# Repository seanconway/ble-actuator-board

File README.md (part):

# BLE Smart-Lock Board: Hardware Design Spec

**Product:** a pocket-sized container with an IoT smart lock. A Hall switch senses the lid, and a small gearmotor drives a locking bar into place. The board talks to a phone app over Bluetooth LE, charges from USB-C, and has no buttons.
**Scope:** prototype PCB rev 1: schematic, off-board parts, layout, and how the board fits into the enclosure
**Status:** layout complete, ERC/DRC clean (KiCad 10), not yet ordered

| Path | Contents |
|---|---|
| `kicad/ble-actuator-board.kicad_pro` | KiCad 10 project: schematic, PCB, custom design rules (`.kicad_dru`) |
| `kicad/easyeda_lib.pretty`, `kicad/easyeda_lib.3dshapes` | Project-local footprints and 3D models (referenced through the project `fp-lib-table`) |
| `bom.csv` | Bill of materials: MPN, LCSC part number, footprint, package, ratings |

This spec is the reference the schematic and layout are checked against. It turns the product requirements into a buildable design: every part, value, footprint, and pin connection, plus layout rules and bring-up. Requirement IDs (`HW-*`, `EN-*`, `FW-*`, `OI-*`, `CM-*`) are defined in [Appendix A](#appendix-a-requirements-referenced) and [Appendix B](#appendix-b-open-items). Items marked **Proposed** are design choices made here that the requirements do not settle.

Datasheet short names: **PS** = nPM1300 Product Specification v1.3, **MDBT** = Raytac MDBT50Q spec Ver. L, **DRV8213** = TI SLVSGV9, **DRV5032** = TI DRV5032. Reference designators are the ones in `kicad/ble-actuator-board.kicad_sch`. Test pads carry signal-name references on the PCB (see §4.10).

**Design rule for this board:** no DNP parts and no 0 Ω resistors except where bench work is expected to need them. DNP is used only to keep JLC from placing a part at a footprint: U4 and M1 (off-board parts whose symbols carry their own wire-pad footprints) and the test pads TP1–TP16 (bare pads, nothing to place). No on-board component footprint is left unpopulated. The board has two fitted 0 Ω resistors: R2 (the VBAT current-measurement link) and R10 (the GAINSEL strap, lifted to change the gain range). The rework options this rule removed, and what each would have bought, are listed in §13.

---

## 1. Block diagram

```
                        ┌──────────────────────── PCB ────────────────────────┐
 USB-C (6-pin) ─ESD─────┤ VBUS ─► nPM1300                                     │
  CC1/CC2 ─ESD──────────┤          ├─ VBAT ◄── R2 ◄──────── J2 (JST-PH) ◄─────┼── 1S LiPo (2-wire)
                        │          ├─ NTC ◄── TH1 (on board)                  │
                        │          ├─ VSYS ─┬─ RGB LED anode                  │
                        │          │        │   cathodes ◄─ LED0/1/2 sinks    │
                        │          ├─ BUCK2 3V0 ─► MDBT50Q VDD/VDDH          │
                        │          │              DRV5032 VDD ────────────────┼── U4 pads → off-board lid sensor
                        │          ├─ BUCK1 VMOT ─► DRV8213 VM + VCC ─► motor ┼── M1 pads → gearmotor (lock)
                        │          ├─ TWI ◄────────► nRF (I²C master)         │
                        │          ├─ GPIO1 (PMIC_INT) ─► nRF                 │
                        │          └─ GPIO0 (NRESETOUT) ─► nRF nRESET         │
                        │                                                     │
                        │ MDBT50Q-P1MV2 ─ PWM ±──► piezo (differential)       │
                        │               ─ IN1/IN2 ─► DRV8213 (auto-sleep)    │
                        │               ◄ nFAULT/nSTALL, IPROPI (ADC)         │
                        │               ◄ HALL_SENSE (GPIO SENSE)             │
                        │               ─ SWD ─► Tag-Connect (J3)             │
                        └─────────────────────────────────────────────────────┘
```

BUCK2 supplies `3V0` because only VSET2 can select 3.0 V at power-up; BUCK1 supplies `VMOT` (§2, D2).

## 2. Datasheet constraints that shape the design

These findings from the datasheets override or refine the original requirements' assumptions. The schematic reflects all of them.

| # | Constraint | Source | Design consequence |
|---|---|---|---|
| D1 | The DRV8213 RTE package has **no nSLEEP pin**. It sleeps when IN1 = IN2 = 0 for t_AUTOSLEEP (0.75–1.05 ms), drawing ≤20 nA on VM and ≤12 nA on VCC. IN1/IN2 have internal 100 kΩ pull-downs. | DRV8213 §6, §8.5.2 | No external pull-downs on IN1/IN2. HW-3 is met by IN1 = IN2 = 0 plus BUCK1 (`VMOT`) off. |
| D2 | **Only VSET2 can select 3.0 V at power-up.** The VSET1 table tops out at 2.7 V (250–500 kΩ); VSET2 selects 3.0 V with 150 kΩ. The resistor must be ≤5% tolerance. | PS Tables 17, 18 | BUCK2 is the always-on `3V0` rail: R3 = 150 kΩ 1% on VSET2 boots it directly at 3.0 V, so no firmware voltage change is needed after a PMIC power cycle. BUCK1 is `VMOT`. |
| D3 | Grounding a VSET pin holds that buck **off at power-up** under software control. | PS §6.3.1 | VSET1 tied directly to GND, so BUCK1 (`VMOT`) stays off until firmware enables it. Matches FW-A1. |
| D4 | DRV8213 **VREF ≤ min(3.3 V, VM − 1.25 V) = 1.75 V** at VM = 3.0 V. With SMODE = Hi-Z the driver ignores VREF and uses 510 mV internally. | DRV8213 §7.3, §8.4.2.2 | VREF comes from a divider on VMOT, never a rail. SMODE is strapped Low so the divider is used. |
| D5 | **ITRIP target is ~40–65 mA, not ~200 mA.** INEED rates the 699:1 at 220 g·cm and the 136:1 at 140 g·cm, both at 60 mA, so ≤150 g·cm sits at or below ~60 mA. 60 mA is the boundary between DRV8213 gain ranges. | INEED motor spec, DRV8213 Table 8-3 | GAINSEL strapped High by fitted 0 Ω R10: 4900 µA/A, accurate over 10–60 mA, OCP ≥160 mA (below the buck's 200 mA rating). This range brackets the ≤150 g·cm point for both gearboxes. The Hi-Z range (60–350 mA) would start the 699:1 at ~220 g·cm, above HW-2. Lift R10 for Hi-Z only if calibration needs more than 60 mA. |
| D6 | nPM1300 watchdog → **NRESETOUT on a GPIO** resets the host without power-cycling BUCK2 (`3V0`). | PS §7.3.2 | GPIO0 wired to nRF nRESET. The RTC survives a watchdog reset. |
| D7 | The VBUS current limit starts at **100 mA** until firmware writes VBUSINILIM0 and TASK.UPDATE.ILIMSW, and reverts on every replug and reset. | PS §6.1.3 | Covered by FW-B6. Firmware reapplies it on each VBUS-insert event. |
| D8 | Module pins 3–14, 50, 52, 54, and 56–61 are **standard drive, low-frequency (≤10 kHz) only**. PWM and I²C do not count as low frequency. | MDBT §2.5–2.6 | The pin map (§5) keeps PWM, I²C, and motor lines off these pins. IPROPI (analog) is allowed there. |
| D9 | VBUSOUT needs a decoupling capacitor even when unused. Unused LDO/load-switch pins go to GND. | PS §6.1.5, Fig 63 | C8 on VBUSOUT; LSIN/LSOUT pins grounded. |
| D10 | The nPM1300 LED pins are 5 mA current sinks. | PS §6.5 | No LED series resistors. |
| D11 | nPM1300 GPIO0/GPIO1 boot as inputs with a 500 kΩ pull-down. On nRESET this draws ~6 µA against the nRF's reset pull-up until firmware makes it an output. | PS §6.6.1 | Firmware configures GPIO0 early in boot (§12). |
| D12 | The DRV8213 tri-level inputs (GAINSEL, IMODE, SMODE) are biased by internal 75 kΩ to VCC and 130 kΩ to GND, and the datasheet does not say whether that bias is switched off in sleep. A hard strap against it would draw ~23 µA (IMODE high) plus ~40 µA (SMODE low). The logic pins (IN1, IN2, GAINSEL, IMODE, SMODE, nFAULT, nSTALL) are rated −0.3 to 5.75 V **to GND, not to VCC**; only TINRUSH (≤ VCC) and IPROPI (≤ VM + 0.3 V) track a supply. The RTE package allows VCC = VM. | DRV8213 §7.1, Fig 8-15 | The whole driver runs from `VMOT`: VCC, IMODE, the GAINSEL strap (R10), and the nFAULT/nSTALL pull-up (R6). With BUCK1 off the driver is unpowered, so strap bias, R6, and R10 draw nothing in sleep. Driving IN1/IN2 while VMOT is off stays within the absolute maximum ratings. |

## 3. Power design

### 3.1 Rails (net names)

| Net | Source | Voltage | Loads | Notes |
|---|---|---|---|---|
| `VBUS` | USB-C (J1) | 5 V | nPM1300 VBUS only | Input limit 500 mA set by firmware (FW-B6, D7) |
| `VBAT` | Battery (J2) through R2 | 3.0–4.2 V | nPM1300 VBAT only | Nothing else may load VBAT (PS §8.2). Charge temperature comes from the board NTC TH1 (§4.2). |
| `VSYS` | nPM1300 pin 20 | ≈VBAT (1 A max) | PVDD, LED anode | Green and blue are fully lit only while VSYS exceeds their Vf plus 0.5 V sink headroom (§4.8) |
| `3V0` | BUCK2 (VOUT2) | 3.0 V (set by VSET2 at power-up) | nRF VDD/VDDH, VDDIO, lid sensor (through R12), I²C and reset pull-ups, Tag-Connect VCC | Always on outside ship mode (D2). Full-board plane on L3 (§7.1). |
| `VMOT` | BUCK1 (VOUT1) | 3.0 V (set by firmware) | DRV8213 VM and VCC, IMODE, GAINSEL strap (R10), nFAULT pull-up (R6), VREF divider | **Enabled only during actuation** (FW-A1, D3). Never feed the motor from VSYS (HW-1). |
| `GND` | — | 0 V | — | Solid plane on L2 (In1.Cu), §7.1 |

### 3.2 Requirements checklist

Checked against the schematic and layout; unchecked items need bench data.

- [ ] BUCK1 (`VMOT`) output capacitance sized for motor inrush. Confirm 200 mA headroom against measured stall current (OI-H1).
- [x] Every buck output capacitor (C10, C6) keeps ≥4 µF effective capacitance at its 3.0 V DC bias, with ESR ≤50 mΩ (PS Table 20). All 10 µF parts are Samsung CL10A106MA8NRNC (X5R 25 V 0603), Nordic's Configuration 1 part. C1 and C12 use the same part.
- [x] DRV8213 VM bulk (C12, 10 µF) and 0.1 µF bypass (C11) placed at the pin.
- [ ] ITRIP set by R7 (R_IPROPI) and the VREF divider so stall current stays below 200 mA **and** stall torque is ≤150 g·cm (HW-2). R7 is 0603 so it can be swapped after bench calibration (OI-H2).
- [x] VREF from a divider on VMOT (R9/R8), ≤1.75 V (D4). It draws nothing while BUCK1 is off.
- [x] DRV8213 sleep relies on IN1 = IN2 = 0 and its internal pull-downs (D1). No external parts.
- [x] DRV8213 VCC, IMODE, R10, and R6 on `VMOT`, so the driver is unpowered whenever BUCK1 is off (D12). SMODE tied to GND.
- [x] nPM1300 GPIO0 wired directly to nRF nRESET (D6).
- [x] Receptacle CC1/CC2 wired directly to nPM1300 CC1/CC2. No discrete pull-downs; the internal Rd presents the sink (HW-11). A 5.1 kΩ in parallel would put the combined Rd (~2.55 kΩ) out of spec.
- [x] SHPHLD routed to a test pad only. It has an internal 50 kΩ pull-up (HW-6).
- [x] nPM1300 GPIO1 routed to an nRF GPIO as the PMIC interrupt (HW-12).
- [ ] Board NTC TH1 (10 kΩ) from the nPM1300 NTC pin to GND with no capacitor >100 pF on it (PS §6.2.4) ✓. **Placement does not yet follow §4.2:** TH1 sits mid-board about 3.5 mm from U2's body, not at the board edge by the battery. Firmware sets 10 kΩ and TH1's β in ADCNTCRSEL.

### 3.3 Sleep current budget (target ≤10 µA average, FW-B4)

| Contributor | Estimate | Source |
|---|---|---|
| nRF52840 System ON, RTC + LFRC, RAM retention | ~2–3 µA | nRF52840 PS |
| nPM1300 quiescent (BUCK2 on, hysteretic mode) | ~1–2 µA (check PS) | nPM1300 PS |
| DRV5032FB | ~0.69 µA typ at 3 V (1.8 µA max; the 0.54 µA figure is at 1.8 V) | DRV5032 PS |
| DRV8213 in sleep | ~0 µA (unpowered: VM and VCC both on `VMOT`) | HW-3, D12 |
| Resistor leakage (pull-ups, VREF divider) | ~0 µA (see §11, sleep-leak audit) | Design |
| LFRC calibration (periodic) | TBD | OI-F10 |
| Leakage (ESD, LED) | TBD | Measure |
| **Total** | **TBD (OI-F7)** | PPK2 on first build, across R2 |

Advertising is budgeted separately (OI-F5).

## 4. Schematic, by subsystem

Passive defaults: `Capacitor_SMD:C_0402_1005Metric` / `Resistor_SMD:R_0402_1005Metric`. **0603** (`C_0603_1608Metric` / `R_0603_1608Metric`) is used for the 10 µF, 2.2 µF, and 1 µF capacitors, for R2, R3, R7, and R10, and for TH1. Every footprint is listed in `bom.csv`.

### 4.1 USB-C input and ESD (J1, D1–D3, C3)

| Ref | Value / part | Footprint | Connections |
|---|---|---|---|
| J1 | **Same Sky UJC-H-G-SMT-2-P6-TR** (LCSC C45343229): USB-C 6-pin power-only, horizontal top-mount. 5 A / 30 V, 10,000 mating cycles. Four through-hole shell legs in plated slots carry the plug load, so the board needs a through-hole solder step for them. | KiCad stock `Connector_USB:USB_C_Receptacle_GCT_USB4125-xx-x-0190_6P_TopMnt_Horizontal`. Checked against the Same Sky recommended layout (datasheet p.3): same pad row (pitches 1.00 / 3.04 / 5.50 mm, widths 0.70 / 0.76 / 0.80 mm, 1.20 mm tall), same four 0.60 × 1.20 mm slots in 1.10 × 1.70 mm pads at 8.64 × 3.80 mm, same 0.68 mm pad offset from the front slots. The 3D model is the GCT part. The receptacle mouth overhangs the board edge by ~0.6 mm. | A9/B9 VBUS → `VBUS`. A12/B12 GND and SH → GND. A5 CC1 → U2.23. B5 CC2 → U2.24. |
| D1 | **LRC LTVS16H12T5G** (LCSC C172439): unidirectional TVS. V_RWM 12 V, V_BR 12.5 V min, V_C 16 V max at 10 A and 23 V max at 60 A (8/20 µs), ±30 kV IEC 61000-4-2. Requirement: unidirectional; V_BR well above the 5.5 V VBUS maximum; clamp < 22 V (nPM1300 VBUS absolute maximum) at the ~30 A peak of an IEC 61000-4-2 8 kV contact strike. This part gives ~19 V at 30 A (datasheet Fig. 3). | Custom `imports:DFN1610-2L_L1.6-W1.0-P1.22` (below) | Pad 1 (cathode) → `VBUS`, pad 2 (anode) → GND. |
| D2, D3 | **onsemi ESD9B5.0ST5G** (LCSC C111566): bidirectional ESD, V_RWM 5.0 V, V_BR 5.8 V min, 15 pF, I_R ≤100 nA, IEC 61000-4-2 ±18 kV. Requirement: V_RWM ≥ 5.0 V and V_BR(min) > 5.5 V (the nPM1300 CC absolute maximum), bidirectional OK. | `Diode_SMD:D_SOD-923` (1.0 × 0.6 mm): machine placement only | D2 on CC1, D3 on CC2, each to GND |
| C3 | 1.0 µF X7R 50 V (Samsung CL10B105KB8NQNC). Requirement: X5R or better, ≥10 V. | 0603 | `VBUS` to GND at U2.21 (PS Table 39 "C1") |

**Why D1 is unidirectional:** VBUS only ever carries positive voltage, but ESD testing (IEC 61000-4-2) and hot-plug ringing hit it with both polarities. The nPM1300's VBUS pin is rated −0.3 V minimum (PS Table 4). A unidirectional TVS conducts forward on a negative strike and holds VBUS to a forward drop: 1.2 V max at 10 mA for D1, rising to a few volts at ESD current. A bidirectional TVS lets VBUS swing to its full negative breakdown (about −8 V) before clamping, which pushes the strike current through the PMIC's own pin-protection instead. Unidirectional parts also clamp lower on positive strikes than bidirectional parts of the same size. CC1/CC2 carry low-current signals and may use either type.

**Why a 12 V working voltage:** the nPM1300 disconnects VBUS above 5.5 V (VBUSOVP, PS §6.1.2) and survives up to 22 V. With V_BR ≥ 12.5 V, a faulty 9 V or 12 V charger only trips the PMIC's overvoltage cutoff, and the TVS does not conduct. A 6–7 V TVS would carry the charger's full current on the same fault until it failed. The trade-off is a higher clamp, which still stays under 22 V at ESD current.

**Why a 5 V working voltage is enough on CC:** with the nPM1300's internal Rd present, CC sits at about 2.1 V or less, even when the charger advertises 3 A. The ESD part must not conduct below the nPM1300's 5.5 V CC absolute maximum, which D2/D3 guarantee through V_BR ≥ 5.8 V. Their working voltage (5.0 V) only sets the leakage rating, which is ≤100 nA and flows only while a cable is attached.

**D1 footprint (DFN1610-2, LRC land pattern, datasheet p.4):** two pads 0.62 × 1.00 mm at 1.22 mm pitch (0.60 mm gap, 1.84 mm overall). Pad 1 = cathode. The part is leadless and needs reflow or hot air.

**Layout (as built)**
- D1, D2, and D3 sit 2–4 mm from the J1 pads, before the traces reach anything else.
- VBUS is routed at 0.5 mm (0.25 mm neck-down at pads), short and direct to U2.21.
- J1's shell slots are on the GND pour.

### 4.2 Battery and charge temperature sensing (J2, BT1, R2, C4, TH1)

| Ref | Value / part | Footprint | Connections |
|---|---|---|---|
| J2 | **JST S2B-PH-SM4-TB(LF)(SN)** (LCSC C295747): 2-pin JST-PH header, 2.0 mm pitch, SMD right-angle. Placed by JLC. Symbol `Device:Battery`, so the cell is drawn by J2 itself. | `Connector_JST:JST_PH_S2B-PH-SM4-TB_1x02-1MP_P2.00mm_Horizontal` | Pin 1 (+) → R2 → `VBAT`. Pin 2 → GND. |
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
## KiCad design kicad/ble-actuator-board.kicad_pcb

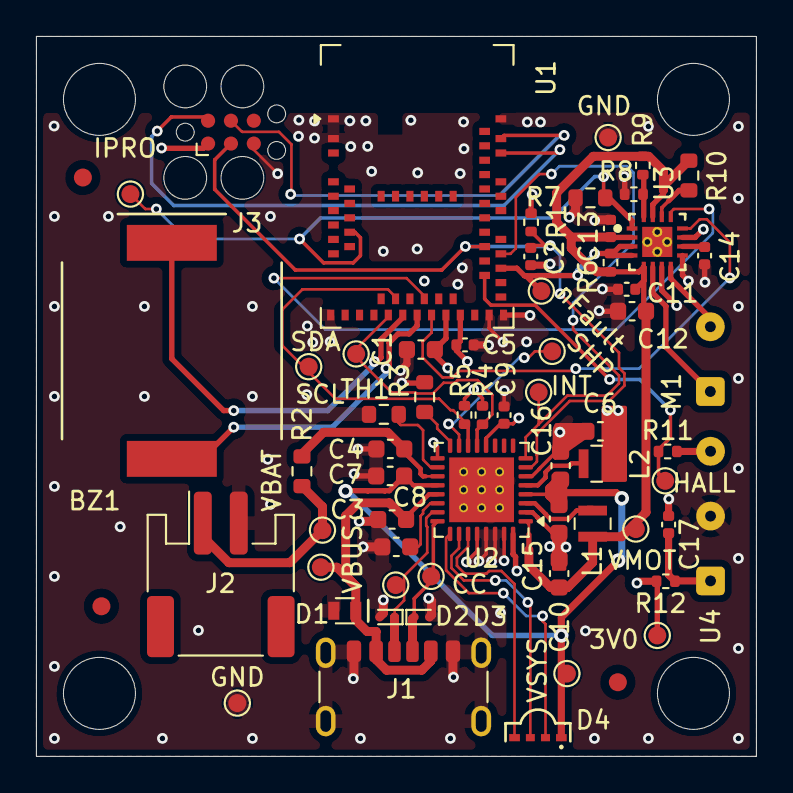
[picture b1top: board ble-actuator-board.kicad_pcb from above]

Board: 4 copper layers, 40.0 x 40.0 mm, 61 parts (0 on the bottom side), 38 nets.

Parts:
3V0: 3V0; TestPoint_Pad_D1.0mm
BZ1: KLJ-1230; BUZ-SMD_L12.0-W12.0
C1, C6, C7, C10, C12, C15, C16: 10uF; C_0603_1608Metric
C2, C5, C9, C11, C13, C17: 100nF; C_0402_1005Metric
C3, C8: 1uF; C_0603_1608Metric
C4: 2.2uF; C_0603_1608Metric
C14: 2.2nF; C_0402_1005Metric
CC: CC2; TestPoint_Pad_D1.0mm
D1: LTVS16H12T5G; DFN1610-2L_L1.6-W1.0-P1.22
D2, D3: ESD9B5.0ST5G; D_SOD-923
D4: NH-B1515RGBA-GF; LED-SMD_4P-L3.2-W1.5_P4-1204RGBWS2-1.5T-A
GND: GND; TestPoint_Pad_D1.0mm
GND#2: GND; TestPoint_Pad_D1.0mm
HALL: HALL_SENSE; TestPoint_Pad_D1.0mm
INT: PMIC_INT; TestPoint_Pad_D1.0mm
IPRO: MOT_IPROPI; TestPoint_Pad_D1.0mm
J1: UJC-H-G-SMT-2-P6-TR; USB_C_Receptacle_GCT_USB4125-xx-x-0190_6P_TopMnt_Horizontal
J2: S2B-PH-SM4-TB; JST_PH_S2B-PH-SM4-TB_1x02-1MP_P2.00mm_Horizontal
J3: Conn_ARM_SWD_TagConnect_TC2030; Tag-Connect_TC2030-IDC-FP_2x03_P1.27mm_Vertical
L1, L2: 2.2uH; L_Inpaq_WIP201610S_2.0x1.6mm
M1: IND-GM-609-699; SolderWire-0.1sqmm_1x02_P3.6mm_D0.4mm_OD1mm
R1, R4, R5, R6: 10k; R_0402_1005Metric
R2, R10: 0R; R_0603_1608Metric
R3: 150k; R_0603_1608Metric
R7: 5.1k; R_0603_1608Metric
R8: 100k; R_0402_1005Metric
R9: 200k; R_0402_1005Metric
R11: 1k; R_0402_1005Metric
R12: 100R; R_0402_1005Metric
SCL: SCL; TestPoint_Pad_D1.0mm
SDA: SDA; TestPoint_Pad_D1.0mm
SHP: SHPHLD; TestPoint_Pad_D1.0mm
TH1: NCP18XH103F03RB; R_0603_1608Metric
TP9: CC1; TestPoint_Pad_D1.0mm
U1: MDBT50Q-P1MV2; Raytac_MDBT50Q
U2: nPM1300-QEAA-R; QFN-32-1EP_5x5mm_P0.5mm_EP3.6x3.6mm_ThermalVias
U3: DRV8213RTER; RTE0016C-MFG
U4: DRV5032FBLPGM; SolderWire-0.1sqmm_1x03_P3.6mm_D0.4mm_OD1mm
VBAT: VBAT; TestPoint_Pad_D1.0mm
VBUS: VBUS; TestPoint_Pad_D1.0mm
VMOT: VMOT; TestPoint_Pad_D1.0mm
VSYS: VSYS; TestPoint_Pad_D1.0mm
nFault: MOT_nFAULT; TestPoint_Pad_D1.0mm

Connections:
/3V0: 3V0.1 (1_1), C1.1, C5.1, C6.1, C9.1, J3.1 (VCC), L2.1, R1.2, R4.2, R5.2, R12.2, U1.28 (VDD), U1.30 (VDDH), U2.12 (VDDIO), U2.32 (VOUT2)
/BUZ_A: BZ1.1 (+), U1.22 (P0.06)
/BUZ_B: BZ1.2 (-), U1.24 (P0.08)
/HALL_SENSE: HALL.1 (1_1), R11.1, U1.36 (P0.14)
/MOT_IN1: U1.25 (P1.08), U3.13 (IN1)
/MOT_IN2: U1.26 (P1.09), U3.12 (IN2)
/MOT_IPROPI: IPRO.1 (1_1), R7.1, U1.11 (P0.02/AIN0), U3.1 (IPROPI)
/MOT_nFAULT: R6.2, U1.37 (P0.13), U3.3 (STALL_N), U3.4 (FAULT_N), nFault.1 (1_1)
/PMIC_INT: INT.1 (1_1), U1.39 (P0.15), U2.8 (GPIO1)
/SCL: R5.1, SCL.1 (1_1), U1.21 (P0.05/AIN3), U2.14 (SCL)
/SDA: R4.1, SDA.1 (1_1), U1.20 (P0.04/AIN2), U2.13 (SDA)
/VBAT: C4.1, R2.1, U2.19 (VBAT)
/VBUS: C3.2, D1.1 (K), J1.A9 (VBUS), J1.B9 (VBUS), U2.21 (VBUS), VBUS.1 (1_1)
/VMOT: C10.1, C11.2, C12.2, C13.2, L1.1, R6.1, R9.2, R10.1, U2.1 (VOUT1), U3.2 (VCC), U3.5 (VM), U3.15 (IMODE), VMOT.1 (1_1)
/VSYS: C7.2, C15.2, C16.1, D4.4 (A), U2.4 (PVDD), U2.20 (VSYS), VSYS.1 (1_1)
/nRESET: C2.1, J3.3 (~RESET), R1.1, U1.40 (P0.18/RESET), U2.7 (GPIO0)
GND: C1.2, C2.2, C3.1, C4.2, C5.2, C6.2, C7.1, C8.2, C9.2, C10.2, C11.1, C12.1, C13.1, C14.1, C15.1, C16.2, C17.1, D1.2 (A), D2.2 (A2), D3.2 (A2), GND.1 (1_1), GND#2.1 (1_1), J1.A12 (GND), J1.B12 (GND), J1.SH (SHIELD), J2.2 (-), J3.5 (GND), R3.1, R7.2, R8.2, TH1.2, U1.1 (GND@1), U1.2 (GND@2), U1.15 (GND@15), U1.32 (VBUS), U1.33 (GND@33), U1.55 (GND@55), U2.2 (PVSS1), U2.6 (PVSS2), U2.17 (VSET1), U2.28 (LSIN1/VINLDO1), U2.29 (LSOUT1/VOUTLDO1), U2.30 (LSIN2/VINLDO2), U2.31 (LSOUT2/VOUTLDO2), U2.33 (AVSS), U3.7 (PGND), U3.9 (GND), U3.11 (SMODE), U3.17 (Thermal_Pad), U4.2 (GND)
unnamed: D2.1 (A1), J1.A5 (CC1), TP9.1 (1_1), U2.23 (CC1)
unnamed: CC.1 (1_1), D3.1 (A1), J1.B5 (CC2), U2.24 (CC2)
unnamed: D4.2 (BK), U2.25 (LED0)
unnamed: D4.1 (GK), U2.26 (LED1)
unnamed: D4.3 (RK), U2.27 (LED2)
unnamed: J2.1 (+), R2.2, VBAT.1 (1_1)
unnamed: J3.4 (SWCLK), U1.53 (SWDCLK)
unnamed: J3.2 (SWDIO), U1.51 (SWDIO)
unnamed: M1.1 (+), U3.6 (OUT1)
unnamed: M1.2 (-), U3.8 (OUT2)
unnamed: TH1.1, U2.18 (NTC)
unnamed: SHP.1 (1_1), U2.15 (SHPHLD)
unnamed: L1.2, U2.3 (SW1)
unnamed: L2.2, U2.5 (SW2)
unnamed: C8.1, U2.22 (VBUSOUT)
unnamed: R3.2, U2.16 (VSET2)
unnamed: R10.2, U3.14 (GAINSEL)
unnamed: C14.2, U3.10 (TINRUSH)
unnamed: R8.1, R9.1, U3.16 (VREF)
unnamed: R11.2, U4.3 (OUT)
unnamed: C17.2, R12.1, U4.1 (VCC)

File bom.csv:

Reference,Qty,Value,Comment,MFR Part #,LCSC Part #,Datasheet,Footprint,Package,Rating,Tolerance,Type,DNP,Notes
BZ1,1,Buzzer,,KLJ-1230,C201042,https://jlcpcb.com/api/file/downloadByFileSystemAccessId/858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,,,,,,,
"C1,C6,C7,C10,C12,C15,C16",7,10uF,10uF 25V X5R 10% 0603,CL10A106MA8NRNC,C96446,https://jlcpcb.com/api/file/downloadByFileSystemAccessId/856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,Capacitor_SMD:C_0603_1608Metric,603,25V,10%,X5R,,25V chosen so buck outputs keep >=4uF at 3V DC bias; C7/C15/C16 need 25V
"C2,C5,C9,C11,C13,C17",6,100nF,100nF 16V X7R 10% 0402,CL05B104KO5NNNC,C1525,https://jlcpcb.com/api/file/downloadByFileSystemAccessId/857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,Capacitor_SMD:C_0402_1005Metric,402,16V,10%,X7R,,C17 is on board at the U4 pads (Hall sensor supply)
"C3,C8",2,1uF,1uF 25V X5R 10% 0603,CL10B105KB8NQNC,C5199872,https://jlcpcb.com/api/file/downloadByFileSystemAccessId/859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,Capacitor_SMD:C_0603_1608Metric,603,25V,10%,X5R,,"On VBUS / VBUSOUT; spec >=10V, 25V preferred"
C4,1,2.2uF,2.2uF 16V X7R 10% 0603,CL10A225KO8NNNC,C23630,https://jlcpcb.com/api/file/downloadByFileSystemAccessId/857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,Capacitor_SMD:C_0603_1608Metric,603,16V,10%,X7R,,VBAT decoupling at U2.19
C14,1,2.2nF,2.2nF 50V C0G 5% 0402,GRM1555C1H222JA01D,C385029,https://jlc-prod-smt.oss-eu-central-1.aliyuncs.com/smtDataMa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,Capacitor_SMD:C_0402_1005Metric,402,50V,5%,C0G/NP0,,TINRUSH timing cap; C0G required for stable timing
D1,1,D_Zener,,LTVS16H12T5G,C172439,https://jlcpcb.com/api/file/downloadByFileSystemAccessId/858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,,,,,,,
"D2,D3",2,D_TVS,,ESD9B5.0ST5G,C111566,https://jlcpcb.com/api/file/downloadByFileSystemAccessId/858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,,,,,,,
D4,1,LED_ABGR,,P4-1204RGBWS2-1.5T-A,C2827295,https://jlcpcb.com/api/file/downloadByFileSystemAccessId/858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,,,,,,,
J1,1,USB_C_Receptacle_PowerOnly_6P,,UJC-H-G-SMT-2-P6-TR,C45343229,https://www.sameskydevices.com/product/resource/ujc-h-g-smt-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,,,,,,,
J2,1,Battery,,S2B-PH-SM4-TB(LF)(SN),C295747,https://jlcpcb.com/api/file/downloadByFileSystemAccessId/858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,,,,,,,
"L1,L2",2,2.2uH,,WIP201610S-2R2ML,C964111,https://jlcpcb.com/api/file/downloadByFileSystemAccessId/860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,,,,,,,
M1,1,Motor_DC,,IND-GM-609-699,-,https://www.ineedmotors.com/Content/upload/pdf/202316849/rd0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,,,,,,DNP,
"R1,R4,R5,R6",4,10k,10k 1% 1/16W 0402,0402WGF1002TCE,C25744,https://jlcpcb.com/api/file/downloadByFileSystemAccessId/855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,Resistor_SMD:R_0402_1005Metric,402,1/16W,1%,Thick film,,
"R2, R10",2,0R,0R jumper 0603,0603WAF0000T5E,C21189,https://jlcpcb.com/api/file/downloadByFileSystemAccessId/875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,Resistor_SMD:R_0603_1608Metric,603,1A,Jumper,Thick film,,VBAT current-measurement link; 0603 per spec
R3,1,150k,150k 1% 1/10W 0603,0603WAF1503T5E,C22807,https://jlc-prod-smt.oss-eu-central-1.aliyuncs.com/smtDataMa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,Resistor_SMD:R_0603_1608Metric,603,1/10W,1%,Thick film,,VSET2 -> BUCK2 = 3.0V at power-up; must be <=5% tolerance
R7,1,5.1k,5.1k 1% 1/10W 0603,0603WAF5101T5E,C23186,https://jlcpcb.com/api/file/downloadByFileSystemAccessId/857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,Resistor_SMD:R_0603_1608Metric,603,1/10W,1%,Thick film,,R_IPROPI: ITRIP ~40mA (High gain); swapped during bench calibration
R8,1,100k,100k 1% 1/16W 0402,0402WGF1003TCE,C25741,https://jlcpcb.com/api/file/downloadByFileSystemAccessId/857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,Resistor_SMD:R_0402_1005Metric,402,1/16W,1%,Thick film,,"VREF divider, 1% required"
R9,1,200k,200k 1% 1/16W 0402,0402WGF2003TCE,C25764,https://jlcpcb.com/api/file/downloadByFileSystemAccessId/857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,Resistor_SMD:R_0402_1005Metric,402,1/16W,1%,Thick film,,"VREF divider, 1% required"
R11,1,1k,1k 1% 1/16W 0402,0402WGF1001TCE,C11702,https://jlc-prod-smt.oss-eu-central-1.aliyuncs.com/smtDataMa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,Resistor_SMD:R_0402_1005Metric,402,1/16W,1%,Thick film,,
R12,1,100R,100R 1% 1/16W 0402,0402WGF1000TCE,C25076,https://jlc-prod-smt.oss-eu-central-1.aliyuncs.com/smtDataMa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,Resistor_SMD:R_0402_1005Metric,402,1/16W,1%,Thick film,,
TH1,1,Thermistor_NTC,,NCP18XH103F03RB,C13564,https://jlcpcb.com/api/file/downloadByFileSystemAccessId/858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,,,,,,,
U1,1,MDBT50Q_1,,MDBT50Q-P1MV2,C5119772,,,,,,,,
U2,1,nPM1300-QEXX,,nPM1300-QEAA-R,C7466043,https://jlcpcb.com/api/file/downloadByFileSystemAccessId/871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,,,,,,,
U3,1,DRV8213RTER,,DRV8213RTER,C31829946,https://www.ti.com.cn/cn/lit/ds/symlink/drv8213.pdf,,,,,,,
U4,1,DRV5032FBLPGM,,DRV5032FBLPGM,C2862715,https://www.ti.com/cn/lit/gpn/drv5032,,,,,,,
